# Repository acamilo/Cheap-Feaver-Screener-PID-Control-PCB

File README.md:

# Cheap-Feaver-Screener-PID-Control-PCB
PCB to control two heating elements wit i2c temp sensors.

Demo Video of version 1 that used a Ceramic Resistor

Demo Video of version 2 that used a PC trace.

# Features
 * USB-C with PD controller to request more power from chargers and battery packs.
 * Two heating element drivers that can drive 3A each.
 * Interfaces with external i2c or Dallas temp sensors.
 * 240x135 TFT display ad 4 buttons for a user interface.
 * Slot for an optional esp8266-01 module for wireless connectivity. (Status, MQTT updates, etc..)
 * Neopixel for indicating status

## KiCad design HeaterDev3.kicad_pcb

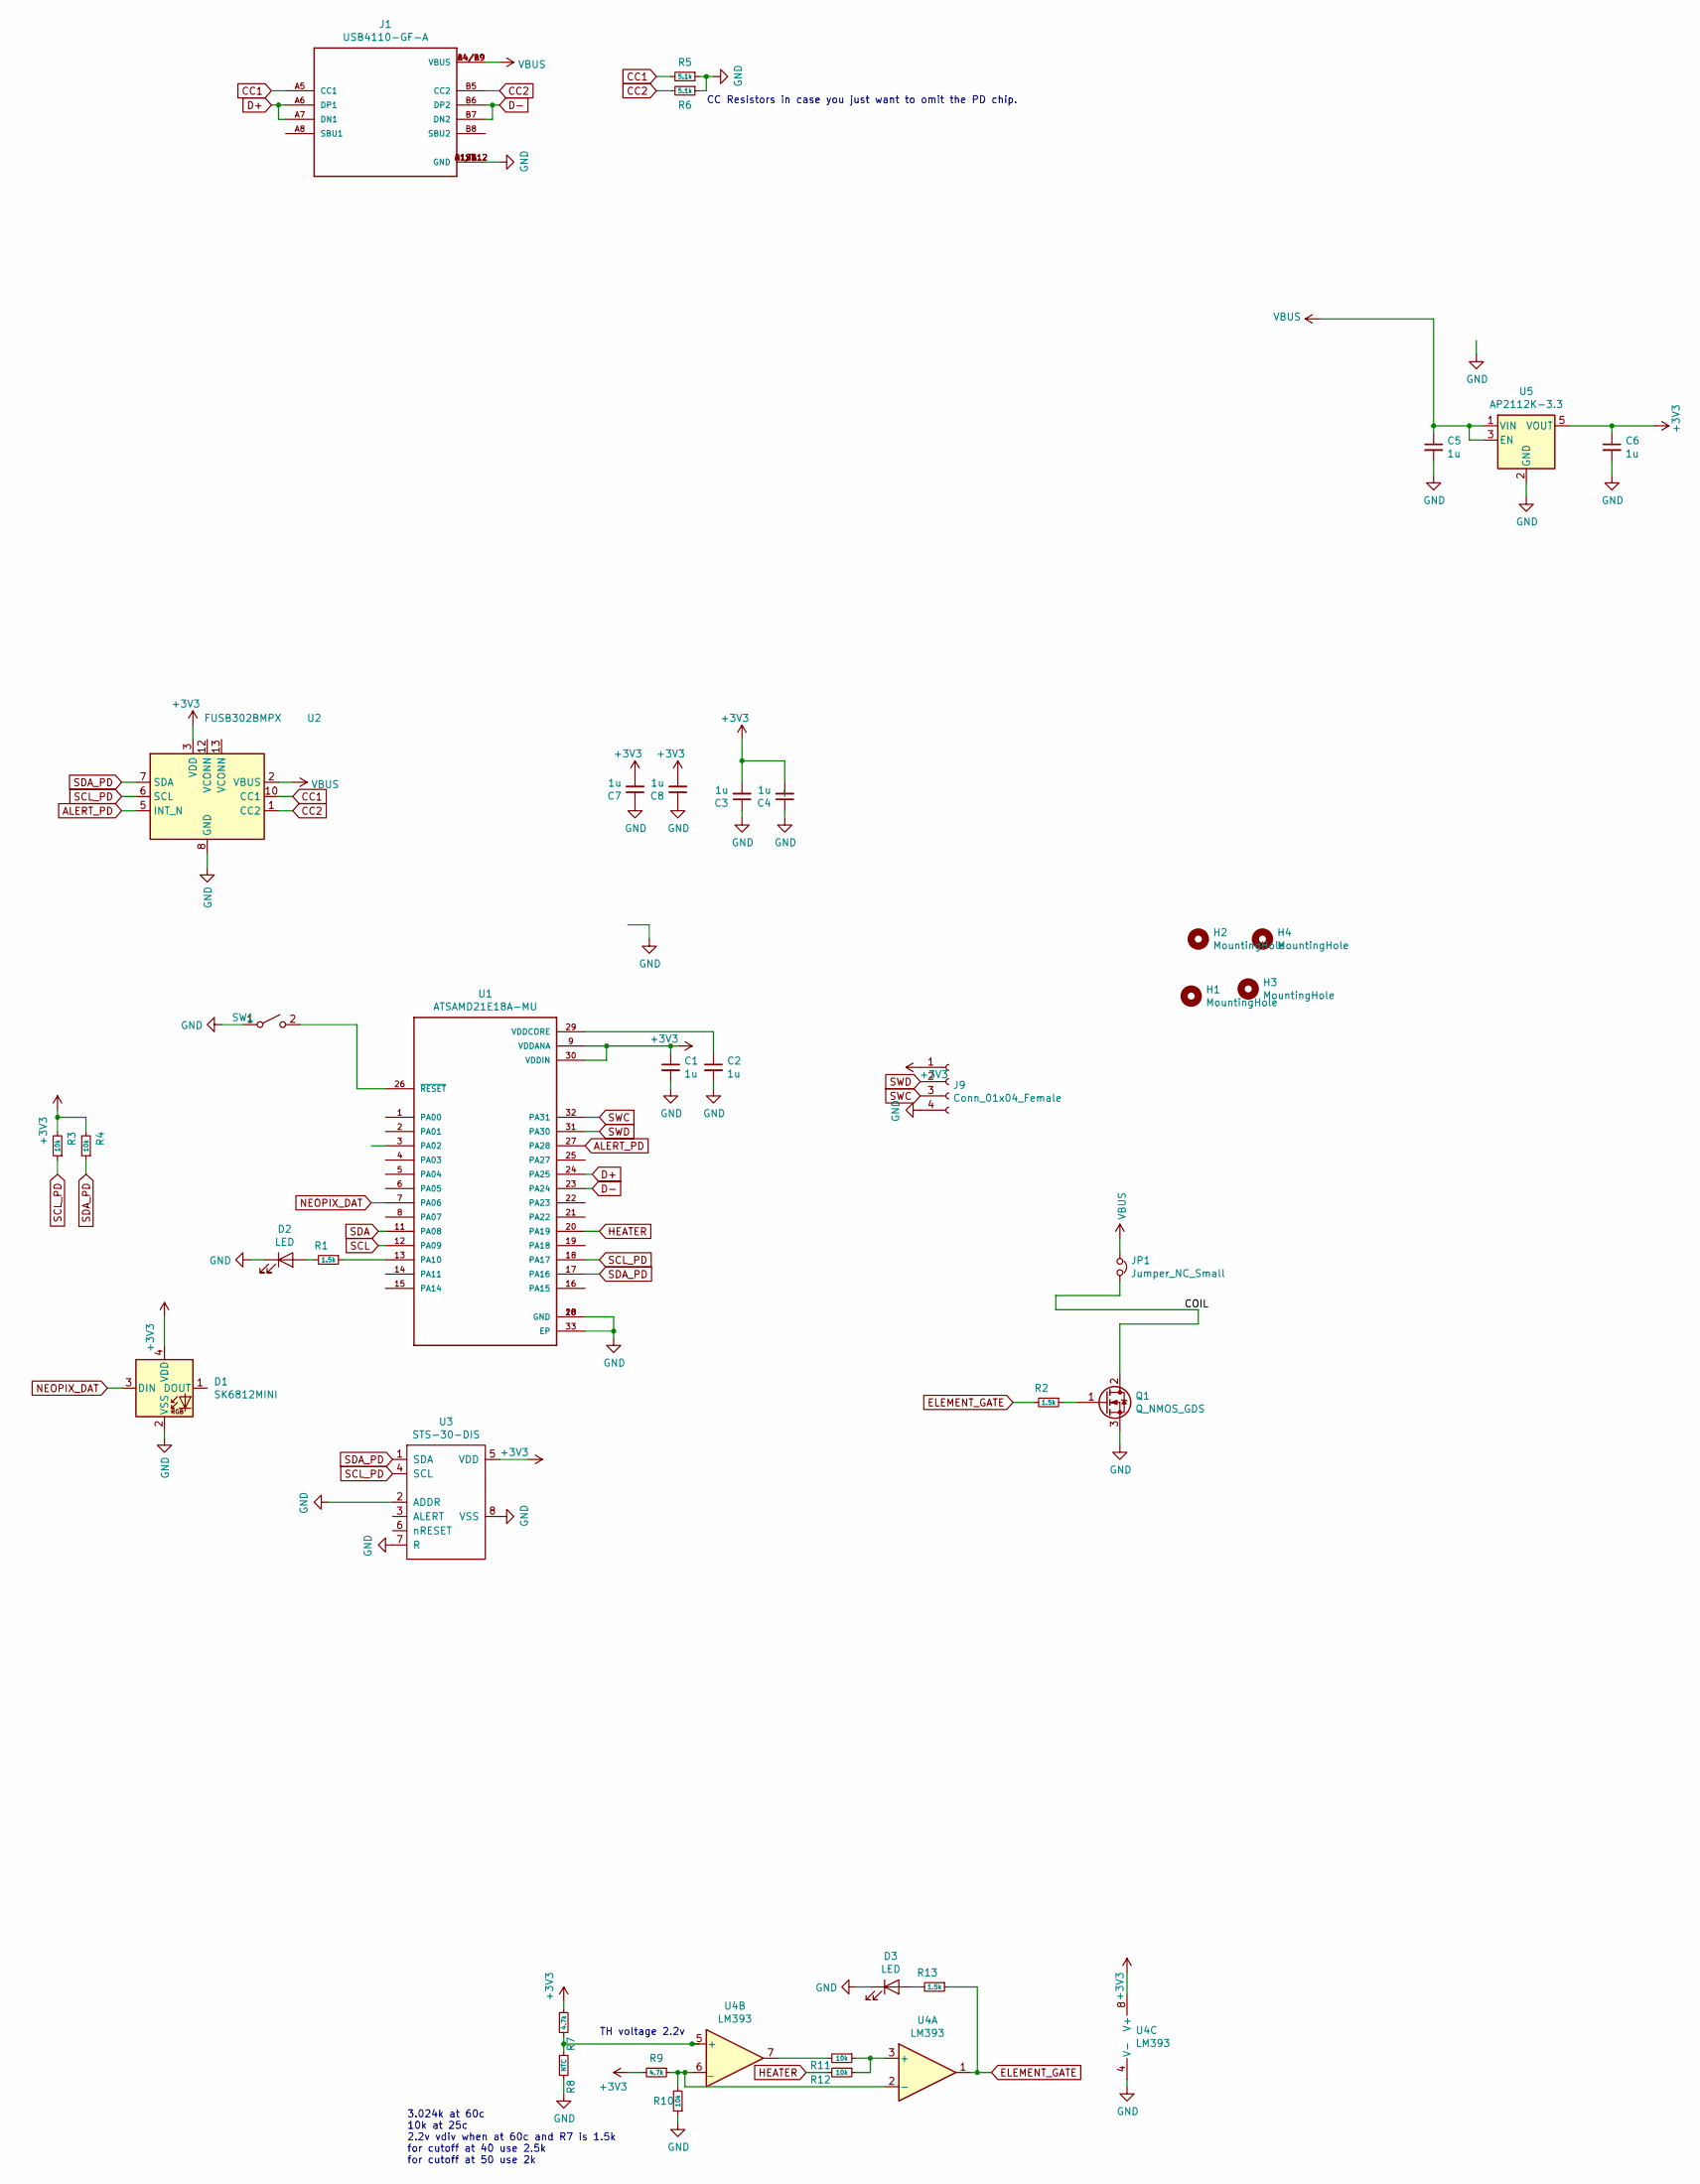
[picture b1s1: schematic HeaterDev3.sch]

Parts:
C1, C2, C3, C4, C5, C6, C7, C8: 1u; C_0603_1608Metric
D1: SK6812MINI; LED_SK6812MINI_PLCC4_3.5x3.5mm_P1.75mm
D2, D3: LED; C_0603_1608Metric
H1, H2, H3, H4: MountingHole; MountingHole_2.2mm_M2
J1: USB4110-GF-A; GCT_USB4110-GF-A
J9: Conn_01x04_Female; PinSocket_1x04_P2.54mm_Vertical
JP1: Jumper_NC_Small; SolderJumper-2_P1.3mm_Bridged_RoundedPad1.0x1.5mm
Q1: Q_NMOS_GDS; SOT-223-3_TabPin2
R1, R2, R13: 1.5k; R_0603_1608Metric
R3, R4, R10, R11, R12: 10k; R_0603_1608Metric
R5, R6: 5.1k; R_0603_1608Metric
R7, R9: 4.7k; R_0603_1608Metric
R8: NTC; R_0603_1608Metric
SW1: SW_SPST; SW_SPST_CK_KXT3
U1: ATSAMD21E18A-MU; QFN50P500X500X100-33N
U2: FUSB302BMPX; WQFN-14-1EP_2.5x2.5mm_P0.5mm_EP1.45x1.45mm
U3: STS-30-DIS; sts
U4: LM393; DFN-8-1EP_2x2mm_P0.45mm_EP0.64x1.38mm
U5: AP2112K-3.3; SOT-23-5

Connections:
+3V3: C1.1, C3.2, C4.2, C6.1, C7.2, C8.2, D1.4 (VDD), J9.1, R3.2, R4.2, R7.1, R9.2, U1.9 (VDDANA), U1.30 (VDDIN), U2.3 (VDD), U2.4 (VDD), U3.5 (VDD), U4.8 (V+), U5.5 (VOUT)
/COIL: JP1.2, Q1.2 (D)
ALERT_PD: U1.27 (PA28), U2.5 (INT_N)
CC1: J1.A5 (CC1), R5.2, U2.10 (CC1), U2.11 (CC1)
CC2: J1.B5 (CC2), R6.2, U2.1 (CC2), U2.14 (CC2)
D+: J1.A6 (DP1), J1.A7 (DN1), U1.24 (PA25)
D-: J1.B6 (DP2), J1.B7 (DN2), U1.23 (PA24)
ELEMENT_GATE: R2.2, R13.1, U4.1
GND: C1.2, C2.2, C3.1, C4.1, C5.2, C6.2, C7.1, C8.1, D1.2 (VSS), D2.1 (K), D3.1 (K), J1.A1/B12 (GND), J1.B1/A12 (GND), J1.S1 (GND), J1.S2 (GND), J1.S3 (GND), J1.S4 (GND), J9.4, Q1.3 (S), R5.1, R6.1, R8.2, R10.1, SW1.1 (A), U1.10 (GND), U1.28 (GND), U1.33 (EP), U2.8 (GND), U2.9 (GND), U2.15 (GND), U3.2 (ADDR), U3.7 (R), U3.8 (VSS), U4.4 (V-), U5.2 (GND)
HEATER: R12.2, U1.20 (PA19)
NEOPIX_DAT: D1.3 (DIN), U1.7 (PA06)
unnamed: C2.1, U1.29 (VDDCORE)
unnamed: D2.2 (A), R1.2
unnamed: D3.2 (A), R13.2
unnamed: Q1.1 (G), R2.1
unnamed: R1.1, U1.13 (PA10)
unnamed: R7.2, R8.1, U4.5 (+)
unnamed: R9.1, R10.2, U4.2 (-), U4.6 (_)
unnamed: R11.1, R12.1, U4.3 (+)
unnamed: R11.2, U4.7
unnamed: SW1.2 (B), U1.26 (~RESET~)
SCL: U1.12 (PA09)
SCL_PD: R3.1, U1.18 (PA17), U2.6 (SCL), U3.4 (SCL)
SDA: U1.11 (PA08)
SDA_PD: R4.1, U1.17 (PA16), U2.7 (SDA), U3.1 (SDA)
SWC: J9.3, U1.32 (PA31)
SWD: J9.2, U1.31 (PA30)
VBUS: C5.1, J1.A4/B9 (VBUS), J1.B4/A9 (VBUS), JP1.1, U2.2 (VBUS), U5.1 (VIN), U5.3 (EN)

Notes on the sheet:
CC Resistors in case you just want to omit the PD chip.
TH voltage 2.2v
3.024k at 60c 10k at 25c 2.2v vdiv when at 60c and R7 is 1.5k for cutoff at 40 use 2.5k for cutoff at 50 use 2k

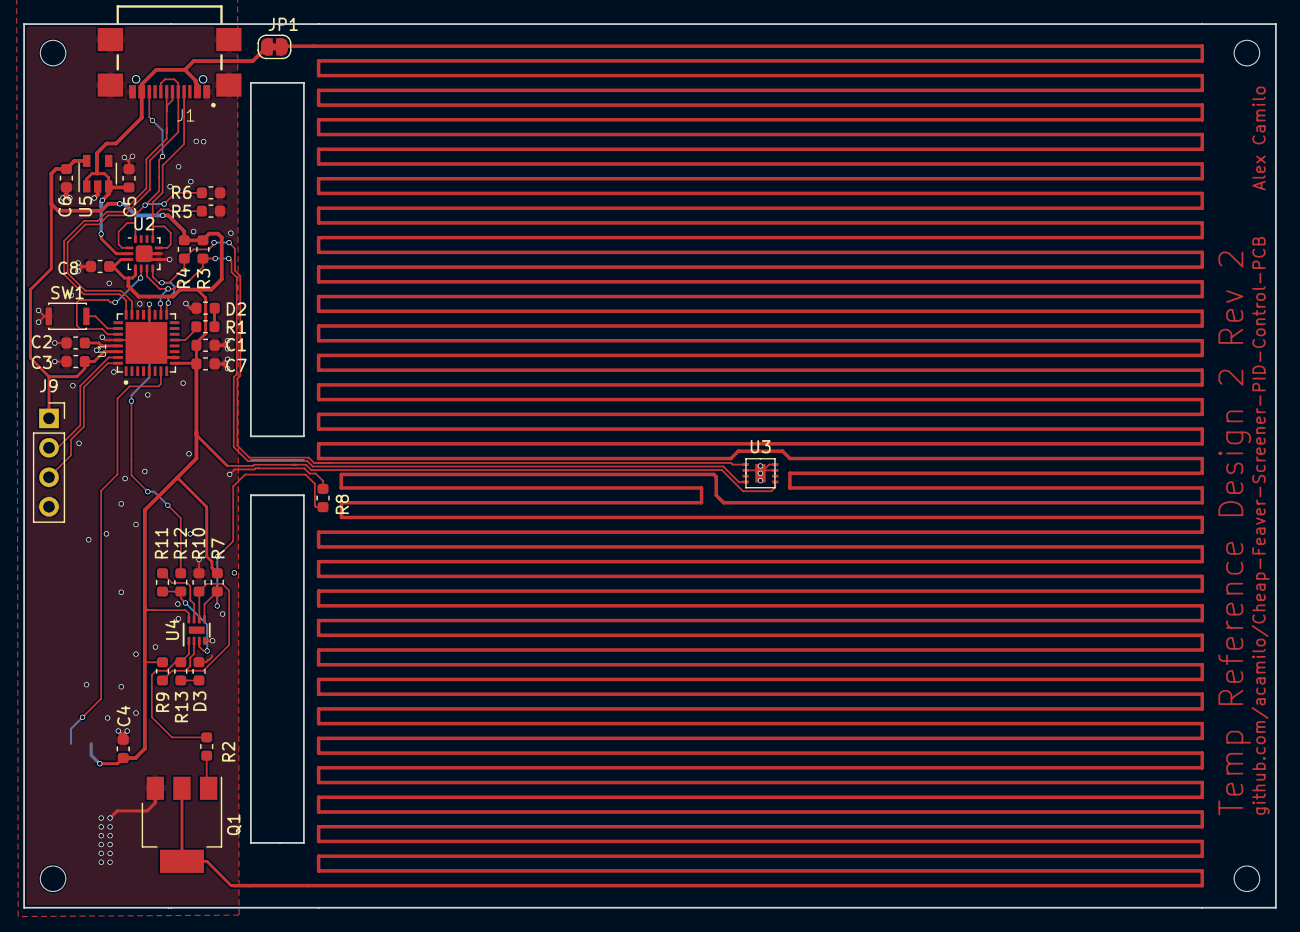
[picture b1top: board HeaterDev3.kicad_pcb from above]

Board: 2 copper layers, 108.0 x 76.2 mm, 38 parts (1 on the bottom side), 26 nets.

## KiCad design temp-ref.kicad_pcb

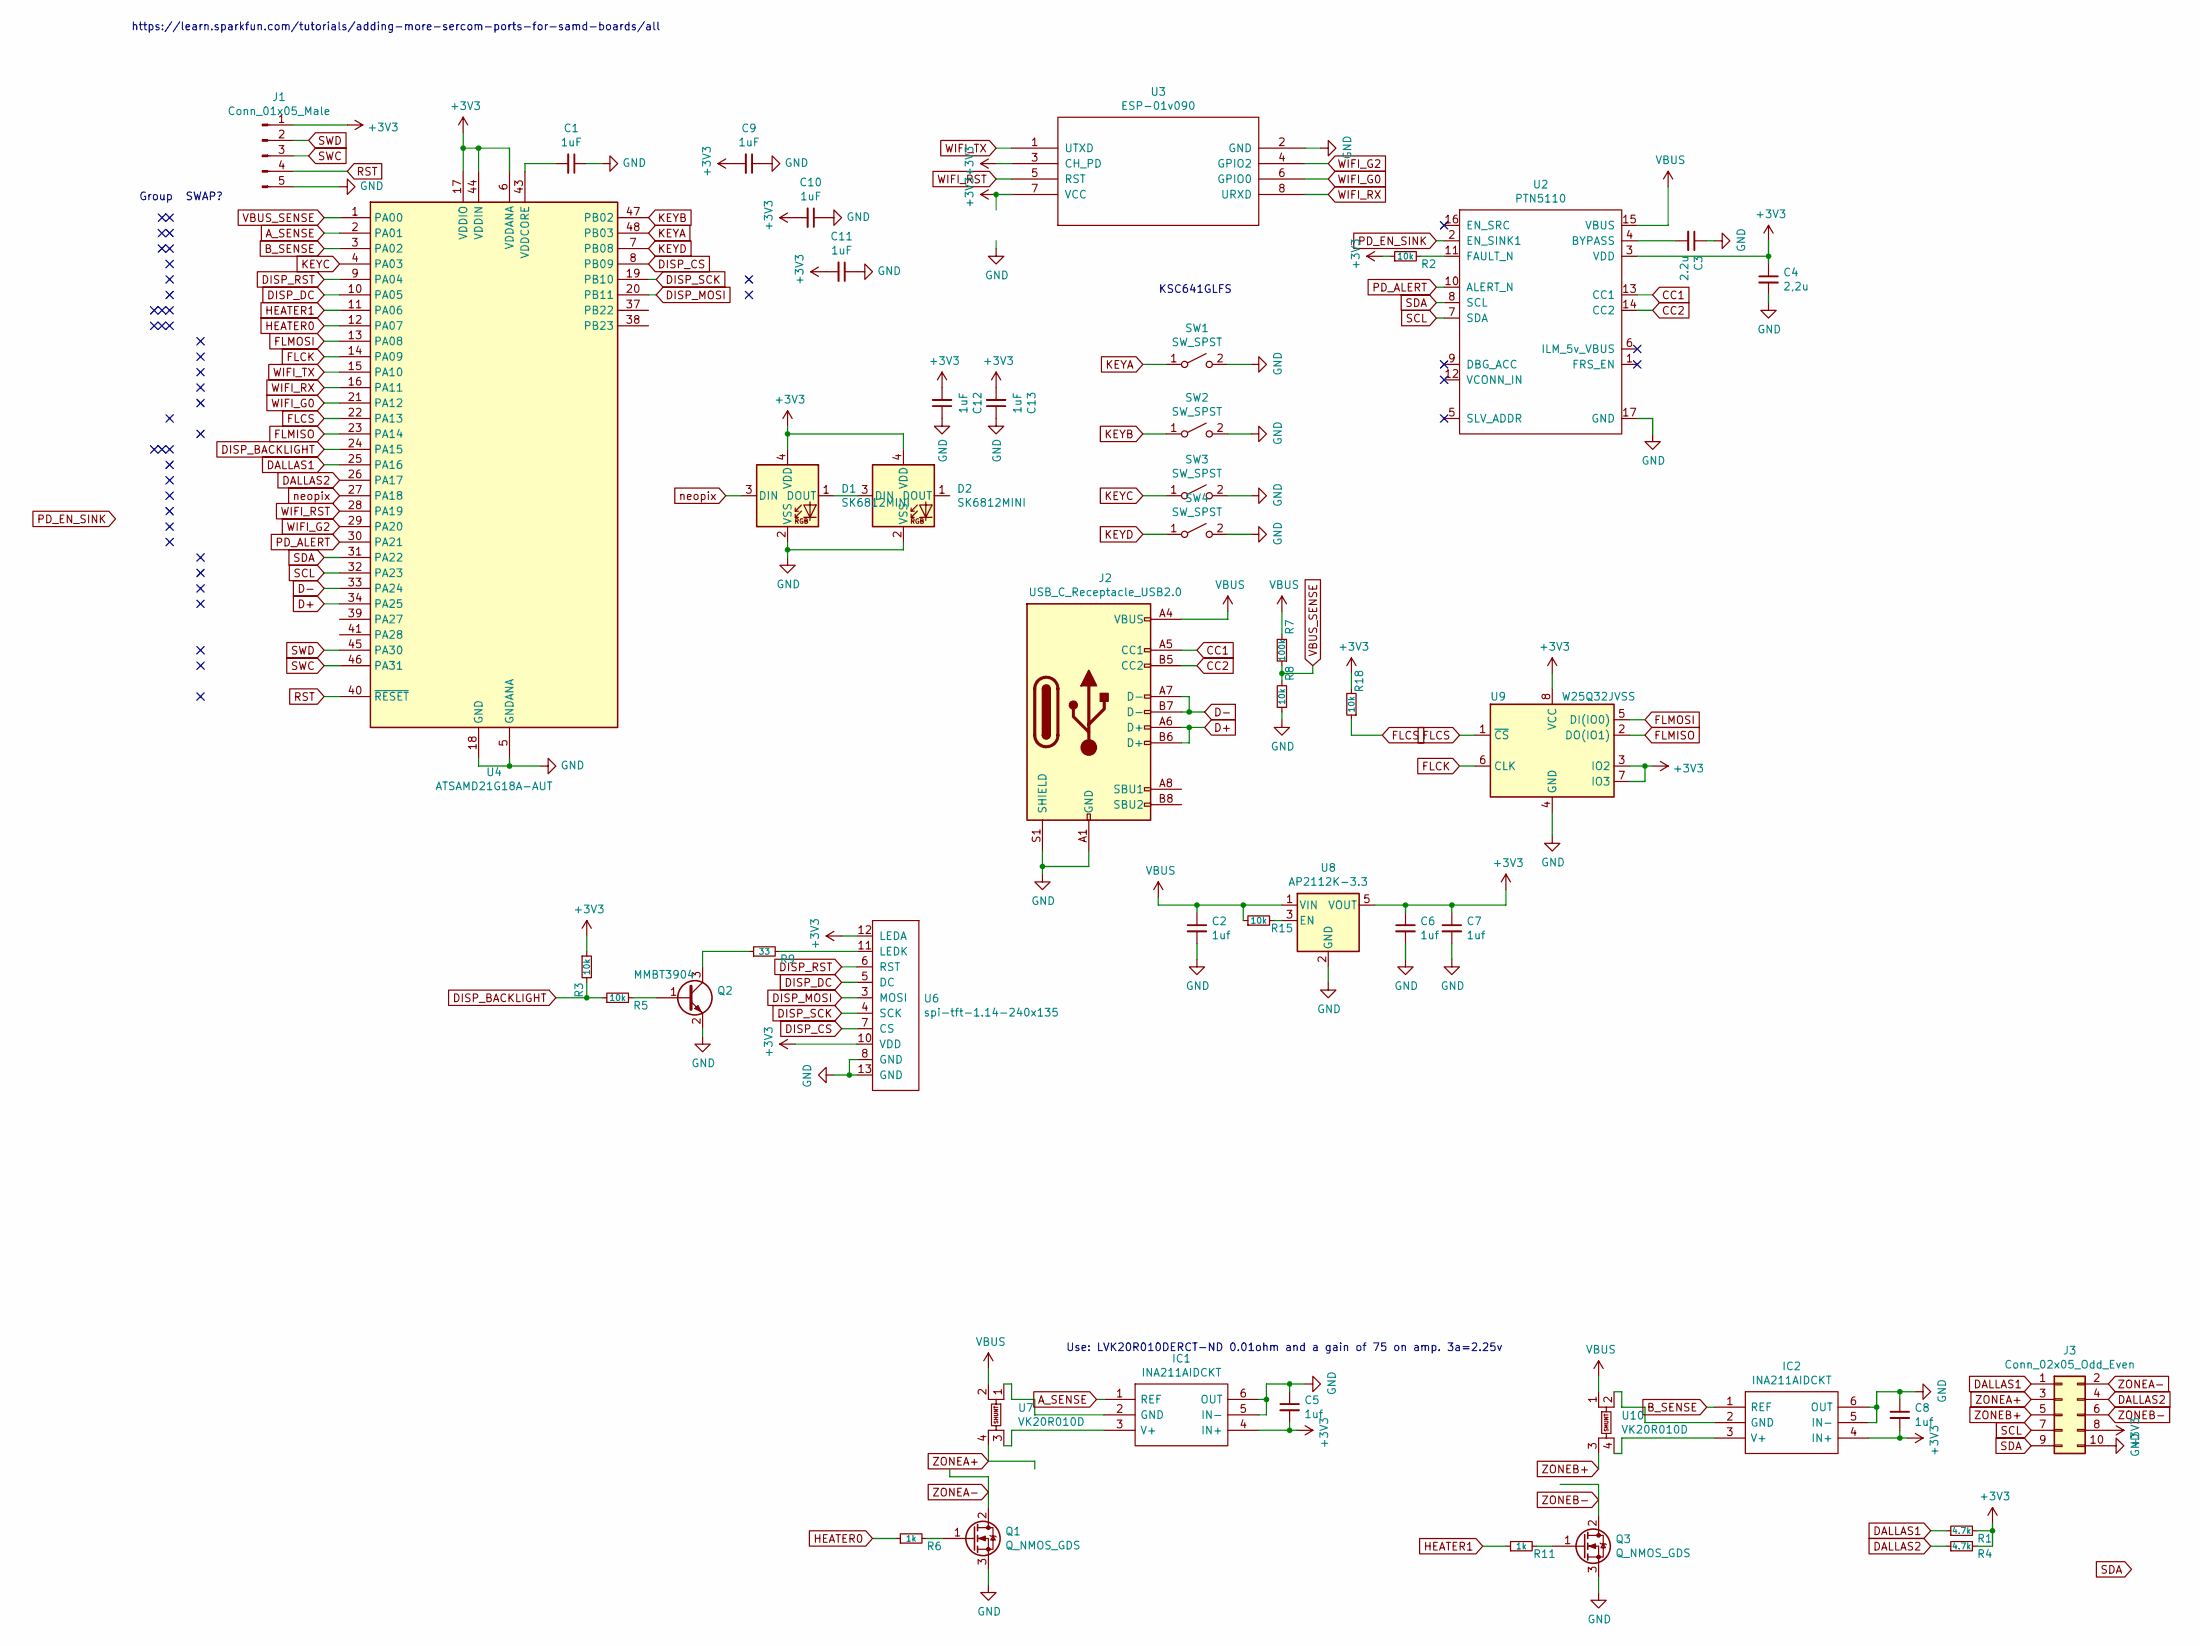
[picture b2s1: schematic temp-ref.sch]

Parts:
C1, C9, C10, C11, C12, C13: 1uF; C_0603_1608Metric
C2, C5, C6, C7, C8: 1uf; C_0603_1608Metric
C3: 2.2u; C_0603_1608Metric
C4: 2,2u; C_0603_1608Metric
D1, D2: SK6812MINI; LED_SK6812MINI_PLCC4_3.5x3.5mm_P1.75mm
IC1, IC2: INA211AIDCKT; SOT65P210X110-6N; Manufacturer_Part_Number INA211AIDCKT; Mouser Part Number 595-INA211AIDCKT
J1: Conn_01x05_Male; PinHeader_1x05_P2.54mm_Vertical
J2: USB_C_Receptacle_USB2.0; USB_C_Receptacle_Amphenol_12401610E4-2A
J3: Conn_02x05_Odd_Even; PinSocket_2x05_P2.54mm_Horizontal
Q1, Q3: Q_NMOS_GDS; SOT-223
Q2: MMBT3904; SOT-23
R1, R4: 4.7k; R_0603_1608Metric
R2, R3, R5, R8, R15, R18: 10k; R_0603_1608Metric
R6, R11: 1k; R_0603_1608Metric
R7: 100k; R_0603_1608Metric
R9: 33; R_0603_1608Metric
SW1, SW2, SW3, SW4: SW_SPST; 5.2mm_Tact_reverse_mount
U2: PTN5110; HX2QFN16
U3: ESP-01v090; ESP-01
U4: ATSAMD21G18A-AUT; QFN-48-1EP_7x7mm_P0.5mm_EP5.3x5.3mm
U6: spi-tft-1.14-240x135; TFT-1.14-240-135
U7, U10: VK20R010D; R_Shunt_Ohmite_LVK12
U8: AP2112K-3.3; SOT-23-5
U9: W25Q32JVSS; SOIC-8_5.23x5.23mm_P1.27mm

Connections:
+3V3: C4.1, C5.2, C6.1, C7.1, C8.2, C9.2, C10.2, C11.2, C12.2, C13.2, D1.4 (VDD), D2.4 (VDD), IC1.4 (IN+), IC2.4 (IN+), J1.1, J3.8, R1.2, R2.1, R3.1, R4.2, R18.2, U2.3 (VDD), U3.3 (CH_PD), U3.7 (VCC), U4.6 (VDDANA), U4.17 (VDDIO), U4.36 (VDDIO), U4.44 (VDDIN), U6.10 (VDD), U6.12 (LEDA), U8.5 (VOUT), U9.3 (IO2), U9.7 (IO3), U9.8 (VCC)
A_SENSE: IC1.1 (REF), U4.2 (PA01)
B_SENSE: IC2.1 (REF), U4.3 (PA02)
CC1: J2.A5 (CC1), U2.13 (CC1)
CC2: J2.B5 (CC2), U2.14 (CC2)
D+: J2.A6 (D+), J2.B6 (D+), U4.34 (PA25)
D-: J2.A7 (D-), J2.B7 (D-), U4.33 (PA24)
DALLAS1: J3.1, R1.1, U4.25 (PA16)
DALLAS2: J3.4, R4.1, U4.26 (PA17)
DISP_BACKLIGHT: R3.2, R5.1, U4.24 (PA15)
DISP_CS: U4.8 (PB09), U6.7 (CS)
DISP_DC: U4.10 (PA05), U6.5 (DC)
DISP_MOSI: U4.20 (PB11), U6.3 (MOSI)
DISP_RST: U4.9 (PA04), U6.6 (RST)
DISP_SCK: U4.19 (PB10), U6.4 (SCK)
FLCK: U4.14 (PA09), U9.6 (CLK)
FLCS: R18.1, U4.22 (PA13), U9.1 (~CS)
FLMISO: U4.23 (PA14), U9.2 (DO(IO1))
FLMOSI: U4.13 (PA08), U9.5 (DI(IO0))
GND: C1.1, C2.2, C3.1, C4.2, C5.1, C6.2, C7.2, C8.1, C9.1, C10.1, C11.1, C12.1, C13.1, D1.2 (VSS), D2.2 (VSS), IC1.5 (IN-), IC1.6 (OUT), IC2.5 (IN-), IC2.6 (OUT), J1.5, J2.A1 (GND), J2.A12 (GND), J2.B1 (GND), J2.B12 (GND), J2.S1 (SHIELD), J3.10, Q1.3 (S), Q2.2 (E), Q3.3 (S), R8.1, SW1.2 (B), SW2.2 (B), SW3.2 (B), SW4.2 (B), U2.17 (GND), U3.2 (GND), U4.5 (GNDANA), U4.18 (GND), U4.35 (GND), U4.42 (GND), U6.8 (GND), U6.13 (GND), U8.2 (GND), U9.4 (GND)
HEATER0: R6.1, U4.12 (PA07)
HEATER1: R11.1, U4.11 (PA06)
KEYA: SW1.1 (A), U4.48 (PB03)
KEYB: SW2.1 (A), U4.47 (PB02)
KEYC: SW3.1 (A), U4.4 (PA03)
KEYD: SW4.1 (A), U4.7 (PB08)
unnamed: C1.2, U4.43 (VDDCORE)
unnamed: C3.2, U2.4 (BYPASS)
unnamed: D1.1 (DOUT), D2.3 (DIN)
unnamed: IC1.2 (GND), U7.1
unnamed: IC1.3 (V+), U7.3
unnamed: IC2.2 (GND), U10.2
unnamed: IC2.3 (V+), U10.4
unnamed: Q1.1 (G), R6.2
unnamed: Q2.1 (B), R5.2
unnamed: Q2.3 (C), R9.1
unnamed: Q3.1 (G), R11.2
unnamed: R2.2, U2.11 (FAULT_N)
unnamed: R9.2, U6.11 (LEDK)
unnamed: R15.2, U8.3 (EN)
PD_ALERT: U2.10 (ALERT_N), U4.30 (PA21)
PD_EN_SINK: U2.2 (EN_SINK1)
RST: J1.4, U4.40 (~RESET)
SCL: J3.7, U2.7 (SDA), U4.32 (PA23)
SDA: J3.9, U2.8 (SCL), U4.31 (PA22)
SWC: J1.3, U4.46 (PA31)
SWD: J1.2, U4.45 (PA30)
VBUS: C2.1, J2.A4 (VBUS), J2.A9 (VBUS), J2.B4 (VBUS), J2.B9 (VBUS), R7.2, R15.1, U2.15 (VBUS), U7.2, U8.1 (VIN), U10.1
VBUS_SENSE: R7.1, R8.2, U4.1 (PA00)
WIFI_G0: U3.6 (GPIO0), U4.21 (PA12)
WIFI_G2: U3.4 (GPIO2), U4.29 (PA20)
WIFI_RST: U3.5 (RST), U4.28 (PA19)
WIFI_RX: U3.8 (URXD), U4.16 (PA11)
WIFI_TX: U3.1 (UTXD), U4.15 (PA10)
ZONEA+: J3.3, U7.4
ZONEA-: J3.2, Q1.2 (D)
ZONEB+: J3.5, U10.3
ZONEB-: J3.6, Q3.2 (D)
neopix: D1.3 (DIN), U4.27 (PA18)

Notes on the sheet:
KSC641GLFS
Use: LVK20R010DERCT-ND 0.01ohm and a gain of 75 on amp. 3a=2.25v
https://learn.sparkfun.com/tutorials/adding-more-sercom-ports-for-samd-boards/all
SWAP?
Group

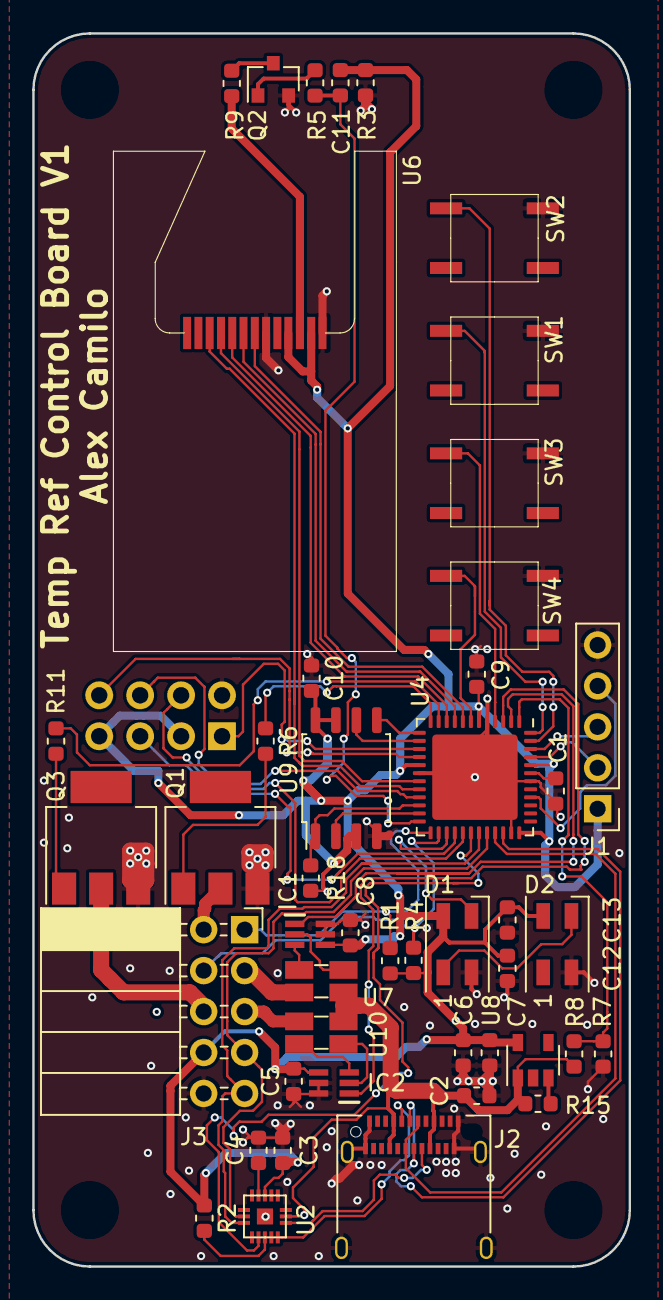
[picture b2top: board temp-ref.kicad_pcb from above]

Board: 2 copper layers, 37.0 x 76.5 mm, 47 parts (1 on the bottom side), 58 nets.

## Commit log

2020-04-25 Committing progress
2020-04-26 Added kicad gitignore
2020-04-26 layout attempt 1
2020-04-26 remove zip and modify gitignore to exclude them in the future
2020-04-26 REworked electronics into smaller board. Heating elements will be seperate.
2020-04-26 Update temp-ref.kicad_pcb
    removed errant via
2020-04-27 3d models added, Added dallas pins, added nepixels, moved some elements around.
2020-04-27 Make cable outline visible on silk
2020-06-18 fixes
2020-06-18 New design with integrated heating element.
2020-06-18 Added cutout for thermal isolation.
2020-06-18 Fixes and changes
    Swapped USB
    Changed heater to PA19
    Removed APA102 and replaced with SK6812MINI on pin PA06
    Changed soldermask clearence
2020-06-18 Added Temperature Cutoff Circuit
2020-06-18 UPDATES?
2020-06-18 Made bridge thicker to pass DRC.
2020-06-21 Swapped out USB Connector for a simpler version.
2020-06-22 Cleaned up routing.
